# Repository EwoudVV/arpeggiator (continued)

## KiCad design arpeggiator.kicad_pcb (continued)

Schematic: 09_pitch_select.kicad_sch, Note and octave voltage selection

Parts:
C502, C503: 100p C0G; C_0805_2012Metric
C561: 100n U502; C_0805_2012Metric
C562: 100n U503; C_0805_2012Metric
U501: OPA4192IDR; SOIC-14_3.9x8.7mm_P1.27mm; MPN OPA4192IDR
U502: ADG706BRUZ; TSSOP-28_4.4x9.7mm_P0.65mm; MPN ADG706BRUZ-REEL7
U503: 74HC4051D; SOIC-16_3.9x9.9mm_P1.27mm; MPN 74HC4051D,653

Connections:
+5V: C561.1, C562.1, U502.1 (VDD), U502.18 (EN), U503.16 (VCC); also elsewhere on the board
NOTE_CV: U501.8 (OUT), U501.9 (-); also elsewhere on the board
unnamed: C502.1, U501.10 (+), U502.28 (D)
unnamed: C503.1, U501.12 (+), U503.3 (Z)
OCTAVE0: U503.11 (S0); also elsewhere on the board
OCTAVE1: U503.10 (S1); also elsewhere on the board
OCT_CV: U501.13 (-), U501.14 (OUT); also elsewhere on the board
PITCH0: U502.17 (A0); also elsewhere on the board
PITCH1: U502.16 (A1); also elsewhere on the board
PITCH2: U502.15 (A2); also elsewhere on the board
PITCH3: U502.14 (A3); also elsewhere on the board
REF1V: U503.14 (Y1); also elsewhere on the board
REF2V: U503.15 (Y2); also elsewhere on the board
TAP1: U502.20 (S2); also elsewhere on the board
TAP2: U502.21 (S3); also elsewhere on the board
TAP3: U502.22 (S4); also elsewhere on the board
TAP4: U502.23 (S5); also elsewhere on the board
TAP5: U502.24 (S6); also elsewhere on the board
TAP6: U502.25 (S7); also elsewhere on the board
TAP7: U502.26 (S8); also elsewhere on the board
TAP8: U502.11 (S9); also elsewhere on the board
TAP9: U502.10 (S10); also elsewhere on the board
TAP10: U502.9 (S11); also elsewhere on the board
TAP11: U502.8 (S12); also elsewhere on the board

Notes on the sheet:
Note and octave voltage selection
The sounding register selects the pitch. Notes are 0 through 11/12V; octaves are 0, 1 or 2V.
U502 enable is active high. U503 inhibit is active high. Unused channels are grounded.

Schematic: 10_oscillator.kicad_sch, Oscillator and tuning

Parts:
C531, C533: 10n; C_0805_2012Metric
C532: 100n; C_0805_2012Metric
C534: 1n C0G; C_0805_2012Metric
R531, R532: 100k 0.01% 25ppm/C; R_0805_2012Metric; MPN RNCF0805TKT100K
R533: 360k 0.1%; R_0805_2012Metric
R534, R542: 1.5M; R_0805_2012Metric
R535: 100k; R_0805_2012Metric
R536, R543: 470; R_0805_2012Metric
R537: 1.5k; R_0805_2012Metric
R538: 24k; R_0805_2012Metric
R539: 5.62k 0.1%; R_0805_2012Metric
R540: 100 0.1%; R_0805_2012Metric
R541: 1M; R_0805_2012Metric
R544: 51k; R_0805_2012Metric
RV501: 500 scale; Potentiometer_Bourns_3296W_Vertical; MPN 3296W-1-501LF
RV502: 10k tempco; Potentiometer_Bourns_3296W_Vertical; MPN 3296W-1-103LF
RV503: 20k HF track; Potentiometer_Bourns_3296W_Vertical; MPN 3296W-1-203LF
U504: AS3340A; DIP-16_W7.62mm; MPN AS3340A

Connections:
+12V: R533.1, R542.1, U504.16 (VCC); also elsewhere on the board
-5V: U504.3 (VEE); also elsewhere on the board
COARSE_CV: R535.1; also elsewhere on the board
FINE_CV: R534.1; also elsewhere on the board
HFT_W: R541.1, RV503.2
NOTE_CV: R531.1; also elsewhere on the board
unnamed: C531.1, R536.2
unnamed: C533.1, R543.2
unnamed: R537.2, RV501.1
unnamed: R538.2, RV502.1
unnamed: R539.2, R540.1
OCT_CV: R532.1; also elsewhere on the board
PULSE: R544.1, U504.4 (PULSE); also elsewhere on the board
REF2V: U504.5 (PWM); also elsewhere on the board
SAW: U504.8 (SAW); also elsewhere on the board
SYNC_REF: U504.9 (SOFT_SYNC); also elsewhere on the board
VCO_CAP: C534.1, U504.11 (TIMING)
VCO_FCI: R531.2, R532.2, R533.2, R534.2, R535.2, R536.1, R541.2, U504.15 (FCI)
VCO_HFT: RV503.1, U504.7 (HF_TRACK)
VCO_LIN: R542.2, R543.1, U504.13 (LIN_FM)
VCO_SCALE: C532.1, R537.1, U504.14 (SCALE)
VCO_T: R539.1, U504.2 (SCALE2)
VCO_Z: R538.1, U504.1 (SCALE1)

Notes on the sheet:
Oscillator and tuning
AS3340A, +12V / -5V. Leave unused hard sync and triangle pins open.
Calibration: set C3, set octave scale, repeat, then check the upper octave. Physical tuning is still required.

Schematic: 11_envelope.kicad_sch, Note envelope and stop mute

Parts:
C601: 100n 5%; C_0805_2012Metric
C602: 10n; C_0805_2012Metric
C603: 1u film 63V 5%; C_Rect_L7.2mm_W5.0mm_P5.00mm; MPN R82DC4100DQ60J
C661: 100n U601; C_0805_2012Metric
Q601, Q605: 2N7002; SOT-23; MPN 2N7002,215
Q602, Q604: MMBT3904; SOT-23; MPN MMBT3904,215
Q603: BSS84; SOT-23; MPN BSS84,215
R601, R602, R605: 100k; R_0805_2012Metric
R603: 18.2k 1%; R_0805_2012Metric
R604, R609: 10k; R_0805_2012Metric
R606, R610: 47k; R_0805_2012Metric
R607, R611: 220; R_0805_2012Metric
R608: 22k; R_0805_2012Metric
RV601: 1M decay; Potentiometer_Alpha_RD901F-40-00D_Single_Vertical; MPN RD901F-40-15F-B1M
U601: TLC555IDR; SOIC-8_3.9x4.9mm_P1.27mm; MPN TLC555IDR
U602: OPA4192IDR; SOIC-14_3.9x8.7mm_P1.27mm; MPN OPA4192IDR

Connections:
+5V: C661.1, Q603.2 (S), R601.1, R603.1, R606.1, U601.8 (VCC); also elsewhere on the board
+12V: R610.1; also elsewhere on the board
AUDIO_ENABLE: R609.1, U601.4 (~RST); also elsewhere on the board
DUMP: Q605.3 (D), R611.1
ENV: C603.1, R607.2, R608.1, R611.2, U602.3 (+)
ENV_BUF: U602.1 (OUT), U602.2 (-); also elsewhere on the board
ENV_CTRL: C602.1, U601.5 (CONT)
ENV_PULSE: R604.1, U601.3 (OUT)
ENV_TRIG: Q601.3 (D), R601.2, U601.2 (TRIG)
MUTE: Q604.3 (C), Q605.1 (G), R610.2
MUTE_B: Q604.1 (B), R609.2
NOTE_TRIGGER: Q601.1 (G), R602.1; also elsewhere on the board
unnamed: Q602.1 (B), R604.2, R605.1
unnamed: Q602.3 (C), Q603.1 (G), R606.2
unnamed: Q603.3 (D), R607.1
unnamed: R608.2, RV601.1

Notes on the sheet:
Note envelope and stop mute
A note starts a 2ms charge pulse. The decay knob sets about 22ms to 1s RC decay.
Stop/reset cancels the charge pulse and discharges the envelope. Film capacitor for C603.

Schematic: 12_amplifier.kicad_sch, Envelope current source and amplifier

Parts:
C621: 100p C0G; C_0805_2012Metric
C622: 33p C0G; C_0805_2012Metric
D601: BAT54GW; D_SOD-123; MPN BAT54GWX
Q606: MMBT3906; SOT-23; MPN MMBT3906,215
R620: 1.82M 0.1%; R_0805_2012Metric
R621, R624: 10k 0.01% 25ppm/C; R_0805_2012Metric; MPN RNCF0805TKY10K0
R622, R623: 100k 0.01% 25ppm/C; R_0805_2012Metric; MPN RNCF0805TKT100K
R625: 10k 0.1%; R_0805_2012Metric
R626: 47k; R_0805_2012Metric
R627: 200k; R_0805_2012Metric
R628: 1k; R_0805_2012Metric
R629: 1M; R_0805_2012Metric
R630: 10k; R_0805_2012Metric
RV602: 100k offset null; Potentiometer_Bourns_3296W_Vertical; MPN 3296W-1-104LF
U602: OPA4192IDR; SOIC-14_3.9x8.7mm_P1.27mm; MPN OPA4192IDR
U604: LM13700M/NOPB; SOIC-16_3.9x9.9mm_P1.27mm; MPN LM13700M/NOPB

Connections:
+5V: R620.1, R621.1, R625.1, RV602.1; also elsewhere on the board
-5V: RV602.3; also elsewhere on the board
ENV_BUF: R623.1; also elsewhere on the board
I_ABC: R630.2, U604.1
I_BASE: D601.2 (A), Q606.1 (B), R626.2
I_EMIT: C621.2, D601.1 (K), Q606.2 (E), R625.2, U602.9 (-)
I_SERVO: C621.1, R626.1, U602.8 (OUT)
I_TARGET: R624.1, U602.7 (OUT), U602.10 (+)
unnamed: Q606.3 (C), R630.1
unnamed: R620.2, R621.2, R622.1, U602.5 (+)
unnamed: R623.2, R624.2, U602.6 (-)
OFFSET_W: R629.1, RV602.2
OTA_SUM: C622.2, R627.2, U602.13 (-), U604.5
OTA_ZERO: R628.1, R629.2, U604.4 (-)
VCA_OUT: C622.1, R627.1, U602.14 (OUT); also elsewhere on the board
WAVE_IN: U604.3 (+); also elsewhere on the board

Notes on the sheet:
Envelope current source and amplifier
U602B makes 5.0025V - ENV/10. The small offset turns the current off at the end of the decay.
R630 limits fault current. D601 limits reverse base-emitter voltage. Adjust RV602 for minimum envelope click.

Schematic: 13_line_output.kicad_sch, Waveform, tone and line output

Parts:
C631, C632: 100n film 100V 5%; C_Rect_L7.2mm_W2.5mm_P5.00mm; MPN R82EC3100DQ70J
C633: 470n film 63V 5%; C_Rect_L7.2mm_W3.5mm_P5.00mm; MPN R82DC3470AA60J
C634: 10n; C_0805_2012Metric
C635: 4.7u 25V X7R; C_0805_2012Metric
J601: 3.5mm mono line out; Jack_PJ-3001F_Vertical; MPN PJ-3001F
R631: 820k; R_0805_2012Metric
R632, R634, R635, R636: 1k; R_0805_2012Metric
R633: 1.1M; R_0805_2012Metric
R637: 100k; R_0805_2012Metric
R638: 6.04k 0.1%; R_0805_2012Metric
R639: 10k 0.1%; R_0805_2012Metric
RV603: 100k tone; Potentiometer_Alpha_RD901F-40-00D_Single_Vertical; MPN RD901F-40-15F-B100K
RV604: 100k audio volume; Potentiometer_Alpha_RD901F-40-00D_Single_Vertical; MPN RD901F-40-15F-A100K
RV605: 100k tune; Potentiometer_Alpha_RD901F-40-00D_Single_Vertical; MPN RD901F-40-15F-B100K
RV606: 100k coarse trim; Potentiometer_Bourns_3296W_Vertical; MPN 3296W-1-104LF
SW601: saw / pulse; SW_Dailywell_1M_SPDT_M2; MPN 1MS1T1B1M2QES
U603: TL074HIDR; SOIC-14_3.9x8.7mm_P1.27mm; MPN TL074HIDR

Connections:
+5V: RV606.1; also elsewhere on the board
-5V: RV606.3; also elsewhere on the board
COARSE_CV: U603.13 (-), U603.14 (OUT); also elsewhere on the board
COARSE_W: RV606.2, U603.12 (+)
FINE_CV: U603.8 (OUT), U603.9 (-); also elsewhere on the board
FINE_W: RV605.2, U603.10 (+)
LINE_BUF: U603.1 (OUT), U603.2 (-); also elsewhere on the board
LINE_OUT: C635.2, J601.T, R637.1; also elsewhere on the board
LINE_SEL: R636.1; also elsewhere on the board
unnamed: C631.2, R631.1
unnamed: C632.2, R633.1
unnamed: C633.2, R635.1
unnamed: C634.1, RV603.1, RV603.2, RV604.3
unnamed: C635.1, R636.2
unnamed: R635.2, RV603.3
unnamed: R633.2, R634.1, SW601.1 (A)
unnamed: R631.2, R632.1, SW601.3 (C)
unnamed: RV604.2, U603.3 (+)
unnamed: R638.2, R639.1, U603.6 (-)
PULSE: C632.1; also elsewhere on the board
REF2V5: RV605.3, U603.5 (+); also elsewhere on the board
SAW: C631.1; also elsewhere on the board
SYNC_REF: R638.1, U603.7 (OUT); also elsewhere on the board
VCA_OUT: C633.1; also elsewhere on the board
WAVE_IN: SW601.2 (B); also elsewhere on the board

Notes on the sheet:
Waveform, tone and line output
Line output for powered speakers or an audio interface. Not a headphone or speaker driver.
The waveform dividers keep the OTA input near +/-5mV. Offset and pitch need bench calibration.

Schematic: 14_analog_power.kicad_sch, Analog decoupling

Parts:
C551, C552: 100n U501; C_0805_2012Metric
C553, C554: 100n U504; C_0805_2012Metric
C555, C556: 100n U602; C_0805_2012Metric
C557, C558: 100n U603; C_0805_2012Metric
C559, C560: 100n U604; C_0805_2012Metric
U501, U602: OPA4192IDR; SOIC-14_3.9x8.7mm_P1.27mm; MPN OPA4192IDR
U603: TL074HIDR; SOIC-14_3.9x8.7mm_P1.27mm; MPN TL074HIDR
U604: LM13700M/NOPB; SOIC-16_3.9x9.9mm_P1.27mm; MPN LM13700M/NOPB

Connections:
+12V: C551.1, C553.1, C555.1, C557.1, C559.1, U501.4 (V+), U602.4 (V+), U603.4 (V+), U604.11 (V+); also elsewhere on the board
-5V: C552.2, C554.2, C556.2, C558.2, C560.2, U501.11 (V-), U602.11 (V-), U603.11 (V-), U604.6 (V-), U604.16; also elsewhere on the board

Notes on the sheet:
Analog decoupling
Analog decoupling. The negative rail is regulated to -5V after the charge pump.
Unused OTA has zero bias current. Unused buffers have grounded inputs and open outputs.

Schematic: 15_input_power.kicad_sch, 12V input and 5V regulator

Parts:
C701: 100u 25V; CP_Radial_D6.3mm_P2.50mm; MPN EEU-FC1E101S
C702: 330n 50V; C_0805_2012Metric
C703: 100n 25V; C_0805_2012Metric
C704: 47u 25V; CP_Radial_D5.0mm_P2.00mm; MPN 25YXJ47M5X11
D701: BZT52C8V2; D_SOD-123; MPN BZT52-C8V2J
D702: SMBJ12A; D_SMB; MPN SMBJ12A
D703: SS14; D_SMA; MPN SS14-E3/61T
F701: MF-MSMF035/33X-2 / 350mA; Fuse_1812_4532Metric; MPN MF-MSMF035/33X-2
J701: PJ-102AH / 12V DC centre +; BarrelJack_PJ102AH_Rear; MPN PJ-102AH
Q701: AO3401A; SOT-23; MPN AO3401A
R701: 100k; R_0805_2012Metric
R729: 910; R_0805_2012Metric
TP701: GND; TestPoint_THTPad_D1.5mm_Drill0.7mm
TP702: +5V; TestPoint_THTPad_D1.5mm_Drill0.7mm
TP703: +12V; TestPoint_THTPad_D1.5mm_Drill0.7mm
U701: L7805CV; TO-220-3_Vertical; MPN L7805CV

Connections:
+5V: C703.1, C704.1, D703.2 (A), R729.1, TP702.1, U701.3 (OUT); also elsewhere on the board
+12V: C701.1, C702.1, D701.1 (K), D702.1 (K), D703.1 (K), Q701.2 (S), TP703.1, U701.1 (IN); also elsewhere on the board
unnamed: D701.2 (A), Q701.1 (G), R701.1
unnamed: F701.1, J701.1
unnamed: F701.2, Q701.3 (D)

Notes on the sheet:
12V input and 5V regulator
Regulated 12V DC only, 5.5 / 2.1mm centre-positive plug. Do not use an unregulated or higher-voltage adapter.
Q701 drain faces the jack. D701 limits Vgs. 5V load budget: 50mA; TO-220 regulator needs airflow.

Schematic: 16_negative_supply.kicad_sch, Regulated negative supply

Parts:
C705, C711: 47u 25V; CP_Radial_D5.0mm_P2.00mm; MPN 25YXJ47M5X11
C706: 100n 50V; C_0805_2012Metric
C707: 100u 25V; CP_Radial_D6.3mm_P2.50mm; MPN EEU-FC1E101S
C708: 1000u 25V; CP_Radial_D10.0mm_P5.00mm; MPN EEU-FR1E102
C709: 2n C0G; C_0805_2012Metric
C717: 100n 25V; C_0805_2012Metric
D704, D707: SS14; D_SMA; MPN SS14-E3/61T
D708: BAT54GW; D_SOD-123; MPN BAT54GWX
R702: 4.7 0.25W; R_1206_3216Metric
R703: 20k 0.1%; R_0805_2012Metric
R704: 174k 0.1%; R_0805_2012Metric
R706: 33k; R_0805_2012Metric
R707: 10k; R_0805_2012Metric
R730: 910; R_0805_2012Metric
TP704: VNEG_RAW; TestPoint_THTPad_D1.5mm_Drill0.7mm
TP705: -5V; TestPoint_THTPad_D1.5mm_Drill0.7mm
U702: LT1054CP; DIP-8_W7.62mm; MPN LT1054CP
U706: L7905CV; TO-220-3_Vertical; MPN L7905CV

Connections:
+12V: R702.1; also elsewhere on the board
-5V: C711.2, C717.2, D704.2 (A), D707.1 (K), R730.2, TP705.1, U706.3 (VO); also elsewhere on the board
CP_FB: C709.1, D708.1 (K), R703.2, R704.1, U702.1 (FB/SHDN)
CP_IN: C705.1, C706.1, R702.2, U702.8 (V+)
CP_KICK: D708.2 (A), R706.2, R707.1
CP_REF: R703.1, U702.6 (VREF)
unnamed: C707.1, U702.2 (CAP+)
unnamed: C707.2, U702.4 (CAP-)
RESET5_N: R706.1; also elsewhere on the board
VNEG_RAW: C708.2, C709.2, D707.2 (A), R704.2, TP704.1, U702.5 (-VOUT), U706.2 (VI)

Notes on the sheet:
Regulated negative supply
Converter target -9.3V. U706 regulates the analog rail to -5V. Negative load budget: 50mA.
C707 positive plate goes to CAP+. C708/C711 positive plates go to ground. Keep pump loops short.

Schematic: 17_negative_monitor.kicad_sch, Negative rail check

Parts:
C713: 100p C0G; C_0805_2012Metric
Q702: MMBT3906; SOT-23; MPN MMBT3906,215
R711: 2k 0.1%; R_0805_2012Metric
R712: 2.32k 0.1%; R_0805_2012Metric
R713: 330k 0.1%; R_0805_2012Metric
R714: 2.2k; R_0805_2012Metric
R715: 47k; R_0805_2012Metric
R716: 100k; R_0805_2012Metric
R717: 10k; R_0805_2012Metric
U703: TL431BIDBZR; SOT-23; MPN TL431BIDBZR

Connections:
+5V: Q702.2 (E), R714.1, R716.1; also elsewhere on the board
-5V: R712.2, U703.3 (A); also elsewhere on the board
NEG_PG: C713.1, Q702.3 (C), R713.1, R717.1; also elsewhere on the board
NMON_REF: R711.2, R712.1, R713.2, U703.2 (REF)
unnamed: Q702.1 (B), R715.2, R716.2
unnamed: R714.2, R715.1, U703.1 (K)

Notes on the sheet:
Negative rail check
TL431B checks the negative rail. The PNP shifts its output up to 5V logic.
Negative rail trip is about -4.6V. R713 adds hysteresis; do not add a capacitor at the TL431 cathode.

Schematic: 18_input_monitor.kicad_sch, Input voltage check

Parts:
C714: 100p C0G; C_0805_2012Metric
Q703: MMBT3906; SOT-23; MPN MMBT3906,215
R721: 6.49k 0.1%; R_0805_2012Metric
R722: 2k 0.1%; R_0805_2012Metric
R723: 330k 0.1%; R_0805_2012Metric
R724: 2.2k; R_0805_2012Metric
R725: 47k; R_0805_2012Metric
R726: 100k; R_0805_2012Metric
R727: 10k; R_0805_2012Metric
U704: TL431BIDBZR; SOT-23; MPN TL431BIDBZR

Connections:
+5V: Q703.2 (E), R724.1, R726.1; also elsewhere on the board
+12V: R721.1; also elsewhere on the board
unnamed: Q703.1 (B), R725.2, R726.2
unnamed: R724.2, R725.1, U704.1 (K)
VIN_PG: C714.1, Q703.3 (C), R723.1, R727.1; also elsewhere on the board
VMON_REF: R721.2, R722.1, R723.2, U704.2 (REF)

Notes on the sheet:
Input voltage check
TL431B checks the protected input. PNP output is high only when the input is high enough.
Input trip is about 10.6V, with about 0.1V hysteresis. Thresholds include resistor and reference tolerances.

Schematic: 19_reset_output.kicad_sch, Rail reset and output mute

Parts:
C715, C716: 100n U705; C_0805_2012Metric
D705: PESD5V0S1BA,115; D_SOD-323; MPN PESD5V0S1BA,115
D706: BAT54S,215; SOT-23; MPN BAT54S,215
R728: 100k; R_0805_2012Metric
TP706: RESET_N; TestPoint_THTPad_D1.5mm_Drill0.7mm
U403, U420: 74HC14; SOIC-14_3.9x8.7mm_P1.27mm; MPN 74HC14D,653
U424: 74HC32; SOIC-14_3.9x8.7mm_P1.27mm; MPN 74HC32D,653
U425: 74HC08; SOIC-14_3.9x8.7mm_P1.27mm; MPN 74HC08D,653
U705: TMUX6219DGKRQ1; VSSOP-8_DGK0008A_TI; MPN TMUX6219DGKRQ1

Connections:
+12V: C715.1, D706.2 (K), U705.4 (VDD), U705.5 (EN); also elsewhere on the board
-5V: C716.2, D706.1 (A), U705.7 (VSS); also elsewhere on the board
AUDIO_ENABLE: R728.1, U705.6 (SEL); also elsewhere on the board
LINE_BUF: U705.8 (S2); also elsewhere on the board
LINE_OUT: D705.1 (A1); also elsewhere on the board
LINE_SEL: D706.3 (COM), U705.1 (D); also elsewhere on the board
NEG_BAD: U403.12, U424.12
NEG_PG: U403.13; also elsewhere on the board
RAILS_BAD: U420.13, U424.11
RAILS_GOOD: U420.12, U425.13
RESET5_N: U425.12; also elsewhere on the board
RESET_N: TP706.1, U425.11; also elsewhere on the board
VIN_BAD: U420.10, U424.13
VIN_PG: U420.11; also elsewhere on the board

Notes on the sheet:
Rail reset and output mute
RESET_N needs 5V reset, valid input and valid negative rail. Existing spare gates are used here.
AUDIO_ENABLE selects the buffered signal; low selects ground. The output resistor limits clamp current.
Place D705 at the jack and keep its ground return short. U705 is a mute switch, not a volume control.

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
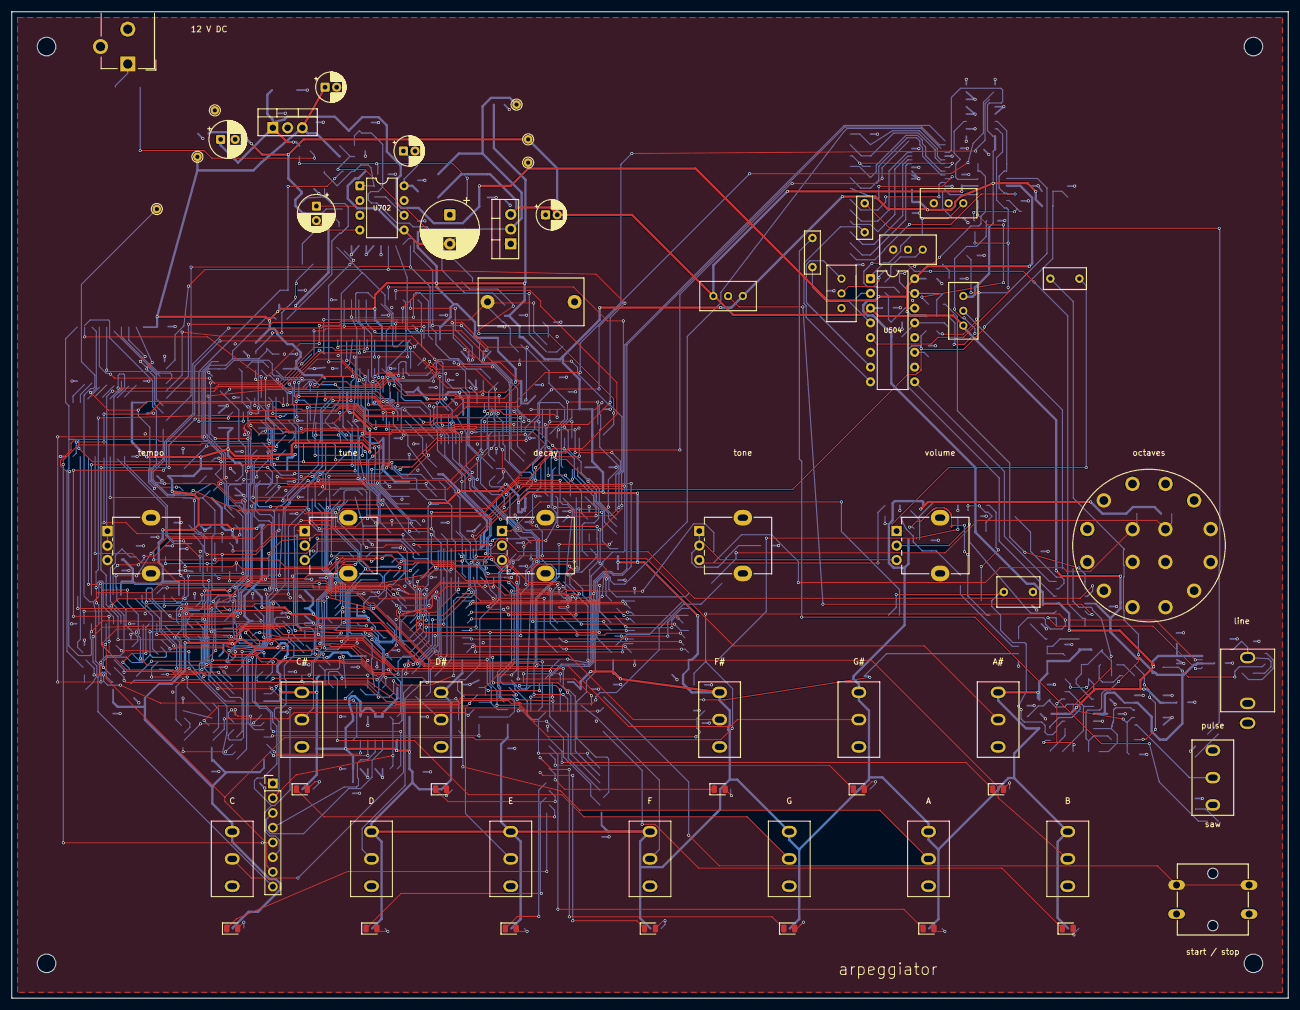
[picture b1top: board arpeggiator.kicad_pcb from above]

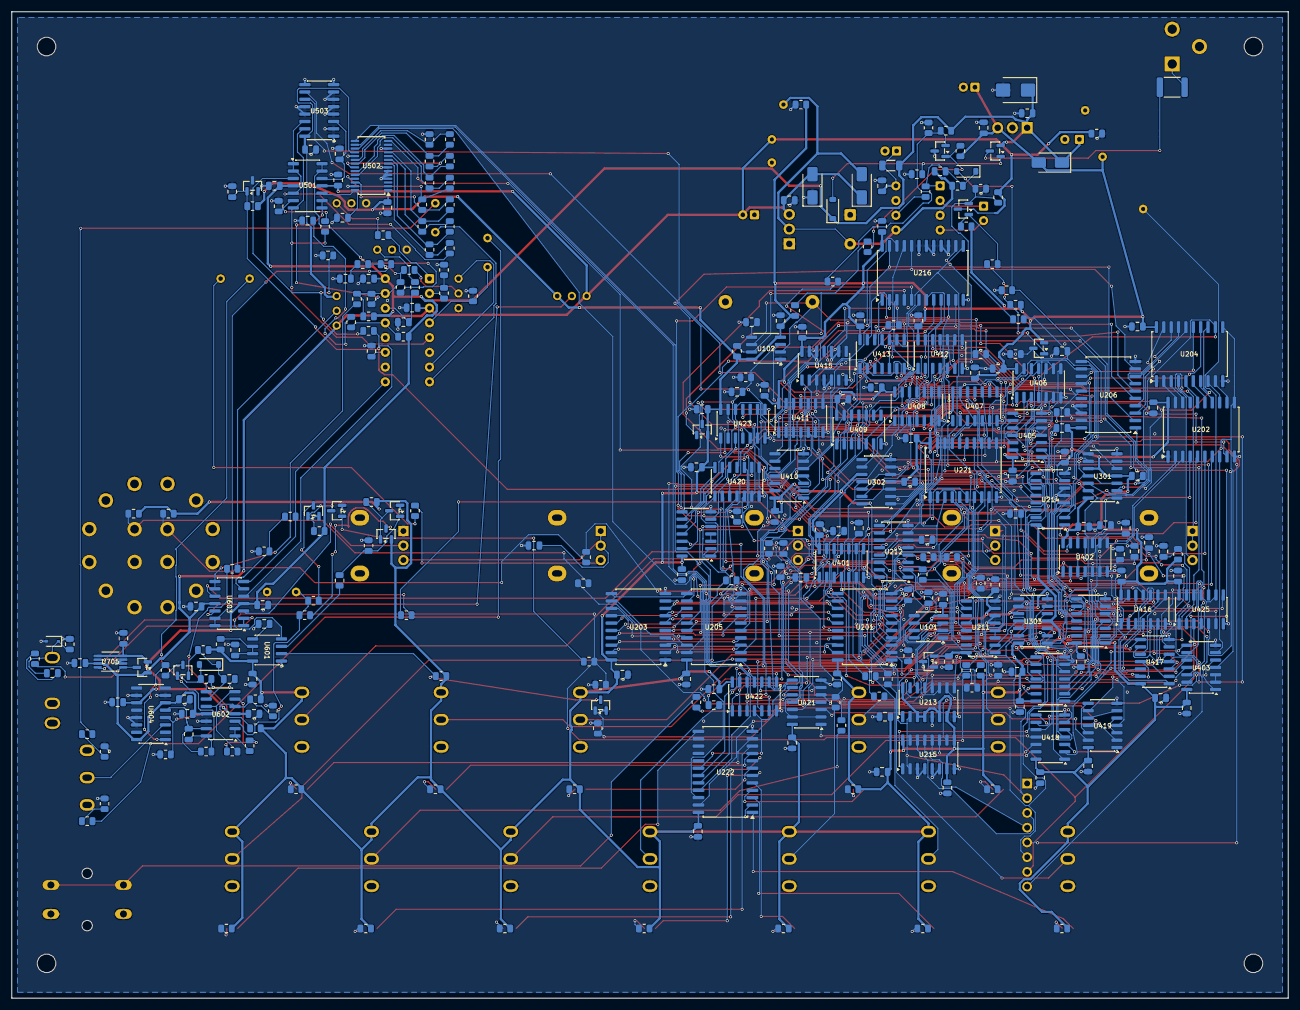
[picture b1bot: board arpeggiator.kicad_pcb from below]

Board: 4 copper layers, 220.0 x 170.0 mm, 360 parts (295 on the bottom side), 365 nets.

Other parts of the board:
H1, H2, H3, H4: M3; MountingHole_3.2mm_M3

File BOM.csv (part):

Value,Quantity,References,MPN,Footprint,Manufacturer,Supplier,Supplier URL,Datasheet,Status
74HC04,4,"U404, U405, U408, U416","74HC04D,653",Package_SO:SOIC-14_3.9x8.7mm_P1.27mm,Nexperia,LCSC,https://www.lcsc.com/product-detail/C5590.html,https://assets.nexperia.com/documents/data-sheet/74HC_HCT04.pdf,"in stock, 23 oct 2026"
74HC08,8,"U406, U413, U414, U417, U418, U421, U423, U425","74HC08D,653",Package_SO:SOIC-14_3.9x8.7mm_P1.27mm,Nexperia,LCSC,https://www.lcsc.com/product-detail/C5593.html,https://assets.nexperia.com/documents/data-sheet/74HC_HCT08.pdf,"in stock, 23 oct 2026"
74HC138,1,U212,"74HC138D,653",Package_SO:SOIC-16_3.9x9.9mm_P1.27mm,Nexperia,LCSC,https://www.lcsc.com/product-detail/C5602.html,https://assets.nexperia.com/documents/data-sheet/74HC_HCT138.pdf,"in stock, 23 oct 2026"
74HC14,4,"U401, U402, U403, U420","74HC14D,653",Package_SO:SOIC-14_3.9x8.7mm_P1.27mm,Nexperia,LCSC,https://www.lcsc.com/product-detail/C5605.html,https://assets.nexperia.com/documents/data-sheet/74HC_HCT14.pdf,"in stock, 23 oct 2026"
74HC154,1,U222,CD74HC154M96,Package_SO:SOIC-24W_7.5x15.4mm_P1.27mm,TI,LCSC,https://www.lcsc.com/product-detail/C2832236.html,https://assets.nexperia.com/documents/data-sheet/74HC_HCT154.pdf,"in stock, 23 oct 2026"
74HC163,4,"U211, U213, U214, U215",SN74HC163DR,Package_SO:SOIC-16_3.9x9.9mm_P1.27mm,TI,LCSC,https://www.lcsc.com/product-detail/C338758.html,https://assets.nexperia.com/documents/data-sheet/74HC_HCT163.pdf,"in stock, 23 oct 2026"
74HC32,7,"U409, U410, U411, U412, U419, U422, U424","74HC32D,653",Package_SO:SOIC-14_3.9x8.7mm_P1.27mm,Nexperia,LCSC,https://www.lcsc.com/product-detail/C5632.html,https://assets.nexperia.com/documents/data-sheet/74HC_HCT32.pdf,"in stock, 23 oct 2026"
74HC377,3,"U205, U206, U221","74HC377D,653",Package_SO:SOIC-20W_7.5x12.8mm_P1.27mm,Nexperia,LCSC,https://www.lcsc.com/product-detail/C5639.html,https://assets.nexperia.com/documents/data-sheet/74HC_HCT377.pdf,"in stock, 23 oct 2026"
74HC4051D,1,U503,"74HC4051D,653",Package_SO:SOIC-16_3.9x9.9mm_P1.27mm,Nexperia,LCSC,https://www.lcsc.com/product-detail/C9386.html,https://assets.nexperia.com/documents/data-sheet/74HC_HCT4051.pdf,"in stock, 23 oct 2026"
74HC574,4,"U201, U203, U202, U204","74HC574D,653",Package_SO:SOIC-20W_7.5x12.8mm_P1.27mm,Nexperia,LCSC,https://www.lcsc.com/product-detail/C16501.html,https://assets.nexperia.com/documents/data-sheet/74HC_HCT574.pdf,"in stock, 23 oct 2026"
74HC74,3,"U301, U302, U303","74HC74D,653",Package_SO:SOIC-14_3.9x8.7mm_P1.27mm,Nexperia,LCSC,https://www.lcsc.com/product-detail/C27597.html,https://assets.nexperia.com/documents/data-sheet/74HC_HCT74.pdf,"in stock, 23 oct 2026"
74HC86,2,"U407, U415","74HC86D,653",Package_SO:SOIC-14_3.9x8.7mm_P1.27mm,Nexperia,LCSC,https://www.lcsc.com/product-detail/C5955.html,https://assets.nexperia.com/documents/data-sheet/74HC_HCT86.pdf,"in stock, 23 oct 2026"
ADG706BRUZ,1,U502,ADG706BRUZ-REEL7,Package_SO:TSSOP-28_4.4x9.7mm_P0.65mm,ADI,LCSC,https://www.lcsc.com/product-detail/C408400.html,https://www.analog.com/media/en/technical-documentation/data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,"in stock, 23 oct 2026"
AS3340A,1,U504,AS3340A,Package_DIP:DIP-16_W7.62mm,ALFA RPAR,Infinite Machinery,https://infinitemachinery.com/as3340a,https://www.alfatriode.lv/eng/sc/AS3340.pdf,"listed in stock, cart blocked by verification"
CD74HC4067M,1,U216,CD74HC4067M,Package_SO:SOIC-24W_7.5x15.4mm_P1.27mm,TI,LCSC,https://www.lcsc.com/product-detail/C1545936.html,https://www.ti.com/lit/ds/symlink/cd74hc4067.pdf,"in stock, 23 oct 2026"
L7805CV,1,U701,L7805CV,Package_TO_SOT_THT:TO-220-3_Vertical,ST,LCSC,https://www.lcsc.com/product-detail/C111887.html,https://www.st.com/resource/en/datasheet/l78.pdf,"in stock, 23 oct 2026"
L7905CV,1,U706,L7905CV,Package_TO_SOT_THT:TO-220-3_Vertical,ST,LCSC,https://www.lcsc.com/product-detail/C111884.html,https://www.st.com/resource/en/datasheet/l79.pdf,"in stock, 23 oct 2026"
LM13700M/NOPB,1,U604,LM13700M/NOPB,Package_SO:SOIC-16_3.9x9.9mm_P1.27mm,TI,LCSC,https://www.lcsc.com/product-detail/C1346265.html,https://www.ti.com/lit/ds/symlink/lm13700.pdf,"in stock, 23 oct 2026"
LT1054CP,1,U702,LT1054CP,Package_DIP:DIP-8_W7.62mm,Texas Instruments,Mouser,https://www.mouser.com/en/ProductDetail/Texas-Instruments/LT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,https://www.ti.com/lit/ds/symlink/lt1054.pdf,"in stock, 22 oct 2026"
MCP100T-450I/TT,1,U103,MCP100T-450I/TT,Package_TO_SOT_SMD:SOT-23,MICROCHIP,LCSC,https://www.lcsc.com/product-detail/C134467.html,https://www.microchip.com/en-us/product/MCP100,"in stock, 23 oct 2026"
OPA4192IDR,2,"U501, U602",OPA4192IDR,Package_SO:SOIC-14_3.9x8.7mm_P1.27mm,TI,LCSC,https://www.lcsc.com/product-detail/C2057908.html,https://www.ti.com/lit/ds/symlink/opa4192.pdf,"in stock, 23 oct 2026"
TL074HIDR,1,U603,TL074HIDR,Package_SO:SOIC-14_3.9x8.7mm_P1.27mm,TI,LCSC,https://www.lcsc.com/product-detail/C2878713.html,https://www.ti.com/lit/ds/symlink/tl074.pdf,"in stock, 23 oct 2026"
TL431BIDBZR,2,"U703, U704",TL431BIDBZR,Package_TO_SOT_SMD:SOT-23,TI,LCSC,https://www.lcsc.com/product-detail/C41283.html,https://www.ti.com/lit/ds/symlink/tl431.pdf,"in stock, 23 oct 2026"
TLC555IDR,3,"U101, U102, U601",TLC555IDR,Package_SO:SOIC-8_3.9x4.9mm_P1.27mm,TI,LCSC,https://www.lcsc.com/product-detail/C6987.html,https://www.ti.com/lit/ds/symlink/tlc555.pdf,"in stock, 23 oct 2026"
TMUX6219DGKRQ1,1,U705,TMUX6219DGKRQ1,Arpeggiator:VSSOP-8_DGK0008A_TI,Texas Instruments,LCSC,https://www.lcsc.com/product-detail/C3657022.html,https://www.ti.com/lit/ds/symlink/tmux6219-q1.pdf,"in stock, 23 oct 2026"
1 / 2 / 3 octaves,1,SW114,SR2612F-0403-18R0B-D8-N,Arpeggiator:SW_Alpha_SR2612F_4P3T,Taiwan Alpha,Tayda,https://www.taydaelectronics.com/electromechanical/switches-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,https://www.taydaelectronics.com/datasheets/A-1892.pdf,"in stock, 22 oct 2026"
1000u 25V,1,C708,EEU-FR1E102,Capacitor_THT:CP_Radial_D10.0mm_P5.00mm,Panasonic,Mouser,https://www.mouser.com/en/ProductDetail/Panasonic/EEU-FR1E10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,,"in stock, 22 oct 2026"
100k 0.01% 25ppm/C,4,"R531, R532, R622, R623",RNCF0805TKT100K,Resistor_SMD:R_0805_2012Metric,SEI Stackpole,Mouser,https://www.mouser.com/en/ProductDetail/SEI-Stackpole/RNCF08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,,"in stock, 22 oct 2026"
100k audio volume,1,RV604,RD901F-40-15F-A100K,Potentiometer_THT:Potentiometer_Alpha_RD901F-40-00D_Single_Vertical,Taiwan Alpha,Tayda,https://www.taydaelectronics.com/100k-ohm-logarithmic-taper-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,https://www.taydaelectronics.com/datasheets/files/A-4728-1.pdf,"in stock, 22 oct 2026"
100k coarse trim,1,RV606,3296W-1-104LF,Potentiometer_THT:Potentiometer_Bourns_3296W_Vertical,BOURNS,LCSC,https://www.lcsc.com/product-detail/C48084.html,https://www.bourns.com/docs/product-datasheets/3296.pdf,"in stock, 23 oct 2026"
100k offset null,1,RV602,3296W-1-104LF,Potentiometer_THT:Potentiometer_Bourns_3296W_Vertical,BOURNS,LCSC,https://www.lcsc.com/product-detail/C48084.html,https://www.bourns.com/docs/product-datasheets/3296.pdf,"in stock, 23 oct 2026"
100k tone,1,RV603,RD901F-40-15F-B100K,Potentiometer_THT:Potentiometer_Alpha_RD901F-40-00D_Single_Vertical,Taiwan Alpha,Tayda,https://www.taydaelectronics.com/100k-ohm-linear-taper-poten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,https://www.taydaelectronics.com/datasheets/files/A-4728-1.pdf,"in stock, 22 oct 2026"
100k tune,1,RV605,RD901F-40-15F-B100K,Potentiometer_THT:Potentiometer_Alpha_RD901F-40-00D_Single_Vertical,Taiwan Alpha,Tayda,https://www.taydaelectronics.com/100k-ohm-linear-taper-poten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,https://www.taydaelectronics.com/datasheets/files/A-4728-1.pdf,"in stock, 22 oct 2026"
100n film 100V 5%,2,"C631, C632",R82EC3100DQ70J,Capacitor_THT:C_Rect_L7.2mm_W2.5mm_P5.00mm,KEMET,Tayda,https://www.taydaelectronics.com/0-1uf-100v-5-kemet-polyeste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,,"in stock, 22 oct 2026"
100u 25V,2,"C701, C707",EEU-FC1E101S,Capacitor_THT:CP_Radial_D6.3mm_P2.50mm,Panasonic,Mouser,https://www.mouser.com/en/ProductDetail/Panasonic/EEU-FC1E10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,https://industrial.panasonic.com/cdbs/www-data/pdf/RDF0000/A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,"in stock, 22 oct 2026"
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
